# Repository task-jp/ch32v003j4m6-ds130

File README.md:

# Gathering CLOCK

Simple two LEDs clock that tells first 5mins in hours.

## Features
* pushing a button in 30 secs resets the clock

|Min|Green|Red|
|---|-----|---|
|0-5|On||
|5-10|Blink||
|10-55||On|
|55-60||Blink|

## Schematic and Layout

## Bill Of Materials
|Ref|Name|Qty|Description|Link|
|---|----|---|-----------|----|
|U1|CH32V003J4M6|1|Micro Controller|[https://akizukidenshi.com/catalog/g/g118062/](https://akizukidenshi.com/catalog/g/g118062/)|
|U2|DS1302+|1|RTC|[https://akizukidenshi.com/catalog/g/g113634/](https://akizukidenshi.com/catalog/g/g113634/)|
|BT1|Battery holder|1|CR2032|[https://akizukidenshi.com/catalog/g/g112908/](https://akizukidenshi.com/catalog/g/g112908/)|
|D1|LED|1|Green|[https://akizukidenshi.com/catalog/g/g106417/](https://akizukidenshi.com/catalog/g/g106417/)|
|D2|LED|1|Red|[https://akizukidenshi.com/catalog/g/g103978/](https://akizukidenshi.com/catalog/g/g103978/)|
|C1,C2|Capacitor|2|0.1uF|[https://akizukidenshi.com/catalog/g/g113374/](https://akizukidenshi.com/catalog/g/g113374/)|
|Y1|Crystal|1|32.768kHz|[https://akizukidenshi.com/catalog/g/g107195/](https://akizukidenshi.com/catalog/g/g107195/)|
|R1|Resistor 0|1|LED limit||
|R2|Resistor 200|1|LED limit|[https://akizukidenshi.com/catalog/g/g106201/](https://akizukidenshi.com/catalog/g/g106201/)|
|SW1|Push Switch|1||[https://akizukidenshi.com/catalog/g/g115969/](https://akizukidenshi.com/catalog/g/g115969/)|

## License
* MIT

## Author
* stasuku@gmail.com

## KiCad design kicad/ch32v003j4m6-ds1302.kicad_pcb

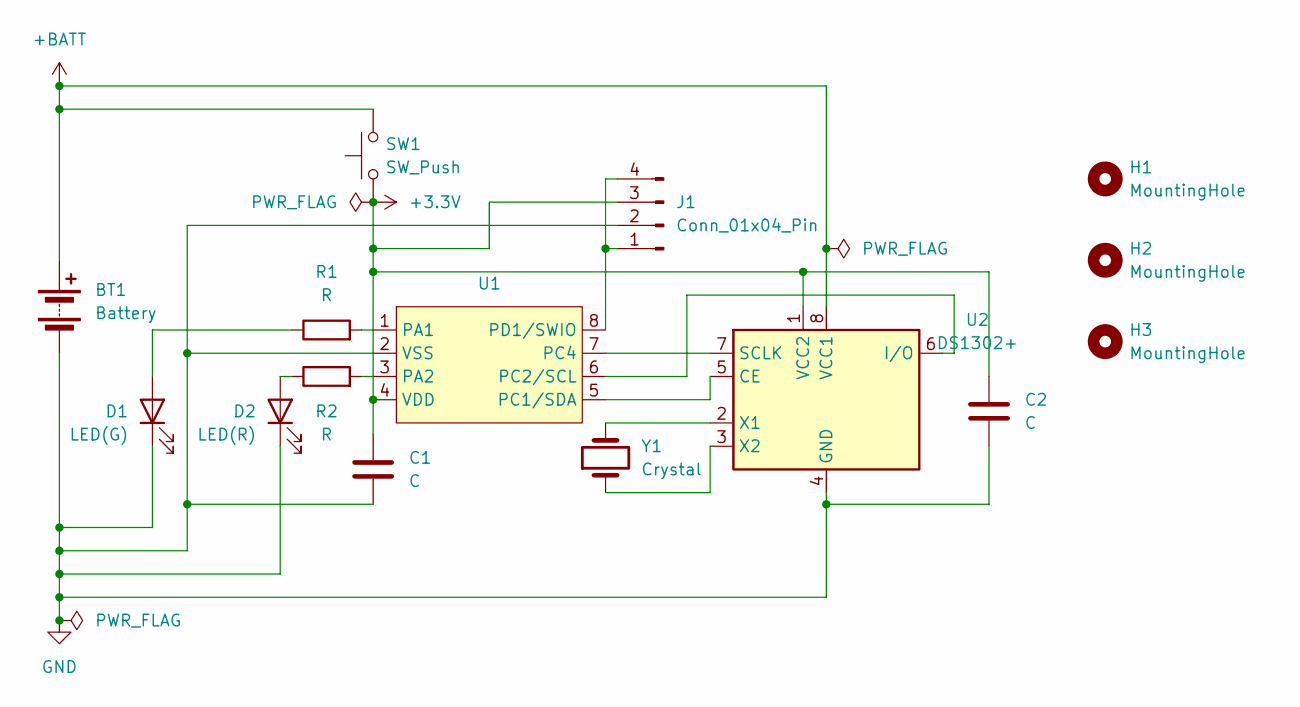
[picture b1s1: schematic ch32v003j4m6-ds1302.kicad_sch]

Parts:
BT1: Battery; BatteryHolder_Keystone_1060_1x2032
C1, C2: C; C_0603_1608Metric
D1: LED(G); LED_0603_1608Metric
D2: LED(R); LED_0603_1608Metric
H1, H2, H3: MountingHole; MountingHole_3.2mm_M3
J1: Conn_01x04_Pin; PinSocket_2x02_P2.54mm_Vertical
R1, R2: R; R_0603_1608Metric
SW1: SW_Push; SW_Push_1P1T_NO_6x6mm_H9.5mm
U1: SOP-8_3.9x4.9mm_P1.27mm
U2: DS1302+; DIP-8_W7.62mm
Y1: Crystal; Crystal_SMD_3215-2Pin_3.2x1.5mm

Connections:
+3.3V: C1.1, C2.1, J1.3, SW1.1, U1.4 (VDD), U2.1 (VCC2)
+BATT: BT1.1 (+), SW1.2, U2.8 (VCC1)
GND: BT1.2 (-), C1.2, C2.2, D1.1 (K), D2.1 (K), J1.2, U1.2 (VSS), U2.4 (GND)
unnamed: D1.2 (A), R1.1
unnamed: D2.2 (A), R2.1
unnamed: J1.1, J1.4, U1.8 (PD1/SWIO)
unnamed: R1.2, U1.1 (PA1)
unnamed: R2.2, U1.3 (PA2)
unnamed: U1.5 (PC1/SDA), U2.5 (CE)
unnamed: U1.6 (PC2/SCL), U2.6 (I/O)
unnamed: U1.7 (PC4), U2.7 (SCLK)
unnamed: U2.2 (X1), Y1.2
unnamed: U2.3 (X2), Y1.1

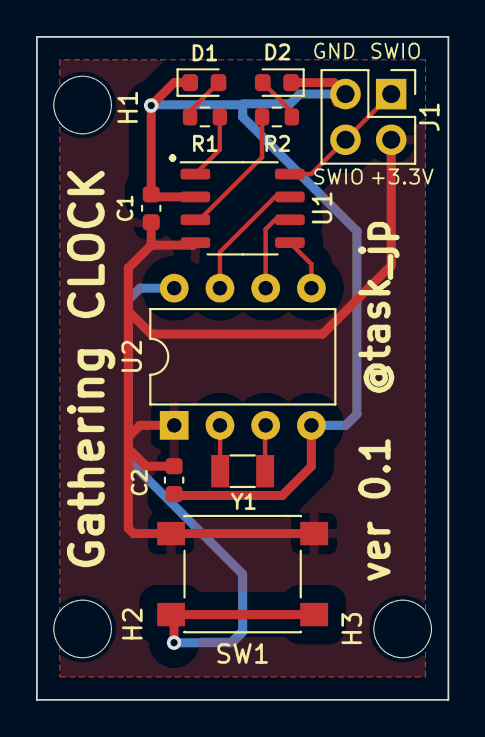
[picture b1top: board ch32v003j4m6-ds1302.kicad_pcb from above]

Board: 2 copper layers, 22.9 x 36.8 mm, 15 parts (1 on the bottom side), 13 nets.

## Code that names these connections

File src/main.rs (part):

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    let gpioa = pac.GPIOA.split(&mut rcc);
    let gpioc = pac.GPIOC.split(&mut rcc);

    let mut green = gpioa.pa1.into_push_pull_output();
    let mut red = gpioa.pa2.into_push_pull_output();

    let sclk = gpioc.pc4.into_push_pull_output();
    let io = gpioc.pc2.into_push_pull_output();
    let ce = gpioc.pc1.into_push_pull_output_in_state(PinState::Low);
    let mut ds1302 = ds1302::Ds1302::new(sclk, io, ce);

    ds1302.set_running(true, &delay).unwrap();
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
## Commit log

2024-01-30 snapshot
2024-01-30 remove reversing when writing
2024-01-31 Add kicad files
2024-01-31 Fix hour in 24 style issue
2024-02-02 Update CAD data
2024-02-02 Add missing symbol library
2024-02-02 Add .gitignore for kicad
2024-02-02 Fix typo
2024-02-02 Fix silk font height and assign +BATT to Power net class
2024-02-02 Add a resistor for LED(G)
2024-02-02 Minimize size
2024-02-05 Fix mouting hole
2024-02-05 Add title to sch
2024-02-26 Fix toolchain
2024-02-26 Run on a real device
2024-02-26 Add README
2024-02-26 Wait 30 secs to reset
2024-02-26 Fix documentation
2024-02-26 Rotate pcb image
2024-02-26 Turn on two LEDs at first
